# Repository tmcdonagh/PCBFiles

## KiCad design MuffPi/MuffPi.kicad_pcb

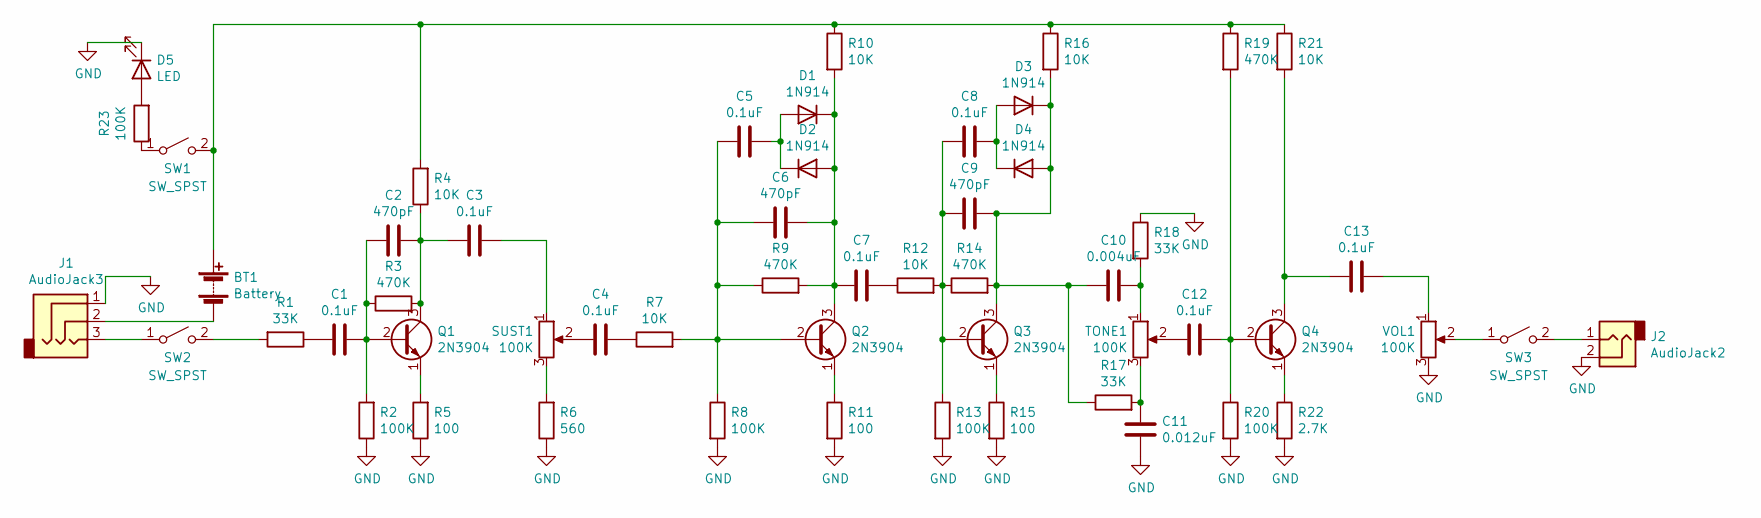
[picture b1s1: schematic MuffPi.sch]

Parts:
BT1: Battery; PinHeader_1x02_P2.00mm_Vertical
C1, C3, C4, C5, C7, C8, C12, C13: 0.1uF; C_Disc_D4.7mm_W2.5mm_P5.00mm
C2, C6, C9: 470pF; C_Disc_D4.3mm_W1.9mm_P5.00mm
C10: 0.004uF; C_Disc_D4.3mm_W1.9mm_P5.00mm
C11: 0.012uF; C_Disc_D4.3mm_W1.9mm_P5.00mm
D1, D2, D3, D4: 1N914; D_DO-35_SOD27_P7.62mm_Horizontal
D5: LED; LED_D3.0mm
J1: AudioJack3; PinHeader_1x03_P2.00mm_Vertical
J2: AudioJack2; PinHeader_1x02_P2.00mm_Vertical
Q1, Q2, Q3, Q4: 2N3904; TO-92_Inline
R1, R17, R18: 33K; R_Axial_DIN0207_L6.3mm_D2.5mm_P10.16mm_Horizontal
R2, R8, R13, R20, R23: 100K; R_Axial_DIN0207_L6.3mm_D2.5mm_P10.16mm_Horizontal
R3, R9, R14, R19: 470K; R_Axial_DIN0207_L6.3mm_D2.5mm_P10.16mm_Horizontal
R4, R7, R10, R12, R16, R21: 10K; R_Axial_DIN0207_L6.3mm_D2.5mm_P10.16mm_Horizontal
R5, R11, R15: 100; R_Axial_DIN0207_L6.3mm_D2.5mm_P10.16mm_Horizontal
R6: 560; R_Axial_DIN0207_L6.3mm_D2.5mm_P10.16mm_Horizontal
R22: 2.7K; R_Axial_DIN0207_L6.3mm_D2.5mm_P10.16mm_Horizontal
SUST1: 100K; PinHeader_1x03_P2.00mm_Vertical
SW1, SW2, SW3: SW_SPST; PinHeader_1x02_P2.00mm_Vertical
TONE1: 100K; PinHeader_1x03_P2.00mm_Vertical
VOL1: 100K; PinHeader_1x03_P2.00mm_Vertical

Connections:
GND: C11.1, D5.1 (K), J1.1, J2.2, R2.1, R5.1, R6.1, R8.2, R11.2, R13.2, R15.2, R18.1, R20.2, R22.2, VOL1.3
unnamed: BT1.1 (+), R4.2, R10.1, R16.1, R19.1, R21.1, SW1.2 (B)
unnamed: BT1.2 (-), J1.2
unnamed: C1.1, C2.2, Q1.2 (B), R2.2, R3.1
unnamed: C1.2, R1.1
unnamed: C2.1, C3.2, Q1.3 (C), R3.2, R4.1
unnamed: C3.1, SUST1.1
unnamed: C4.1, R7.1
unnamed: C4.2, SUST1.2
unnamed: C5.1, D1.2 (A), D2.1 (K)
unnamed: C5.2, C6.2, Q2.2 (B), R7.2, R8.1, R9.1
unnamed: C6.1, C7.2, D1.1 (K), D2.2 (A), Q2.3 (C), R9.2, R10.2
unnamed: C7.1, R12.1
unnamed: C8.1, D3.2 (A), D4.1 (K)
unnamed: C8.2, C9.2, Q3.2 (B), R12.2, R13.1, R14.1
unnamed: C10.1, R18.2, TONE1.1
unnamed: C9.1, C10.2, D3.1 (K), D4.2 (A), Q3.3 (C), R14.2, R16.2, R17.1
unnamed: C11.2, R17.2, TONE1.3
unnamed: C12.1, TONE1.2
unnamed: C12.2, Q4.2 (B), R19.2, R20.1
unnamed: C13.1, Q4.3 (C), R21.2
unnamed: C13.2, VOL1.1
unnamed: D5.2 (A), R23.2
unnamed: J1.3, SW2.1 (A)
unnamed: J2.1, SW3.2 (B)
unnamed: Q1.1 (E), R5.2
unnamed: Q2.1 (E), R11.1
unnamed: Q3.1 (E), R15.1
unnamed: Q4.1 (E), R22.1
unnamed: R1.2, SW2.2 (B)
unnamed: R6.2, SUST1.3
unnamed: R23.1, SW1.1 (A)
unnamed: SW3.1 (A), VOL1.2

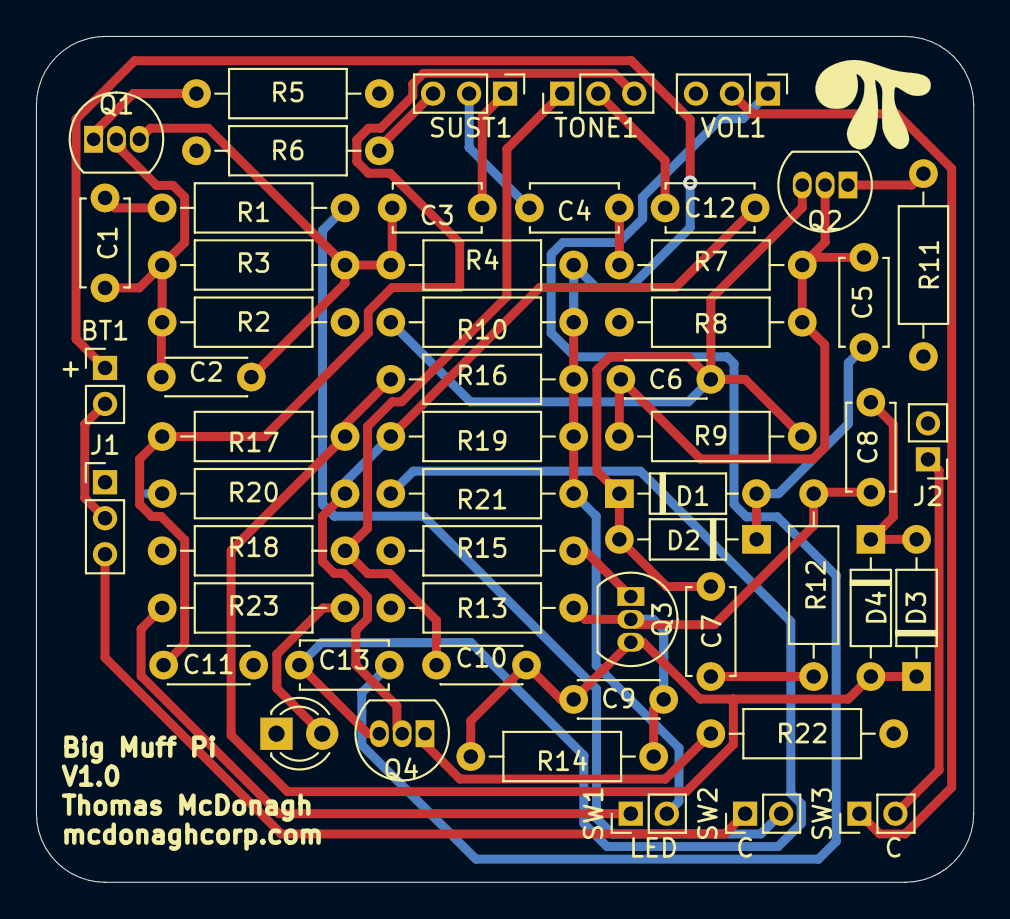
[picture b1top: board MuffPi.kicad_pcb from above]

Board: 2 copper layers, 52.1 x 47.0 mm, 54 parts (0 on the bottom side), 33 nets.

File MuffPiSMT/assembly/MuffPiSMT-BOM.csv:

Value,Designator,Footprint,LCSC Part #
100nF,"C1,C3,C4,C5,C7,C8,C12,C13",0603,C14663
4.7nF,C10,0603,C53987
0.012uF,C11,0603,C1593
470pF,"C2,C6,C9",0603,C1620
1N914,"D1,D2,D3,D4",SOD-323F,C258181
2N3904,"Q1,Q2,Q3,Q4",SOT-23-3,C18536
33K,"R1,R17,R18",0603,C4216
100K,"R2,R8,R13,R20,R23",0603,C25803
2.7K,R22,0603,C13167
470K,"R3,R9,R14,R19",0603,C23178
10K,"R4,R7,R10,R12,R16,R21",0603,C25804
100,"R5,R11,R15",0603,C7250
560,R6,0603,C23189
,,,
,,,
,,,
,,,

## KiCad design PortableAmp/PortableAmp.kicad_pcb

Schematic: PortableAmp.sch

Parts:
C1: 100uF; CP_Axial_L18.0mm_D6.5mm_P25.00mm_Horizontal
C2, C4: 47nF; C_Flat_L7.2_H6.5
C3: 100nF; C_Flat_L7.2_H6.5
C5: 220uF; CP_Axial_L10.0mm_D6.0mm_P15.00mm_Horizontal
D1: D; D_DO-41_SOD81_P10.16mm_Horizontal
H1, H2, H3, H4: Mount; MountingHole_2.7mm_Pad
J1: Conn_01x04_Male; PinSocket_1x04_P2.54mm_Vertical
J2: Speaker; PinSocket_1x02_P2.54mm_Vertical
Q1: MPF102; TO-92L_Inline
R1: 1.5M; R_Axial_DIN0207_L6.3mm_D2.5mm_P10.16mm_Horizontal
R2: 3.9K; R_Axial_DIN0207_L6.3mm_D2.5mm_P10.16mm_Horizontal
R3: 10; R_Axial_DIN0207_L6.3mm_D2.5mm_P10.16mm_Horizontal
RV1: 10K-B; Potentiometer_Bourns_3386F_Vertical
RV2: 1K-B; Potentiometer_Bourns_3386F_Vertical
SW1: Power; PinHeader_1x02_P2.54mm_Vertical
U1: LM386; DIP-8_W7.62mm

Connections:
9V: J1.4, SW1.1
GND: C1.2, C3.1, C4.2, H1.1, H2.1, H3.1, H4.1, J1.1, J1.2, J2.1, R1.2, R2.2, RV1.1, U1.3 (+), U1.4 (GND)
Input: J1.3, Q1.3 (G), R1.1
unnamed: C1.1, D1.1 (K), Q1.1 (D), U1.6 (V+)
unnamed: C2.1, Q1.2 (S), R2.1
unnamed: C2.2, RV1.3
unnamed: C3.2, U1.7 (BYPASS)
unnamed: C4.1, R3.2
unnamed: C5.1, R3.1, U1.5
unnamed: C5.2, J2.2
unnamed: D1.2 (A), SW1.2
unnamed: RV1.2, U1.2 (-)
unnamed: RV2.1, U1.8 (GAIN)
unnamed: RV2.2, RV2.3, U1.1 (GAIN)

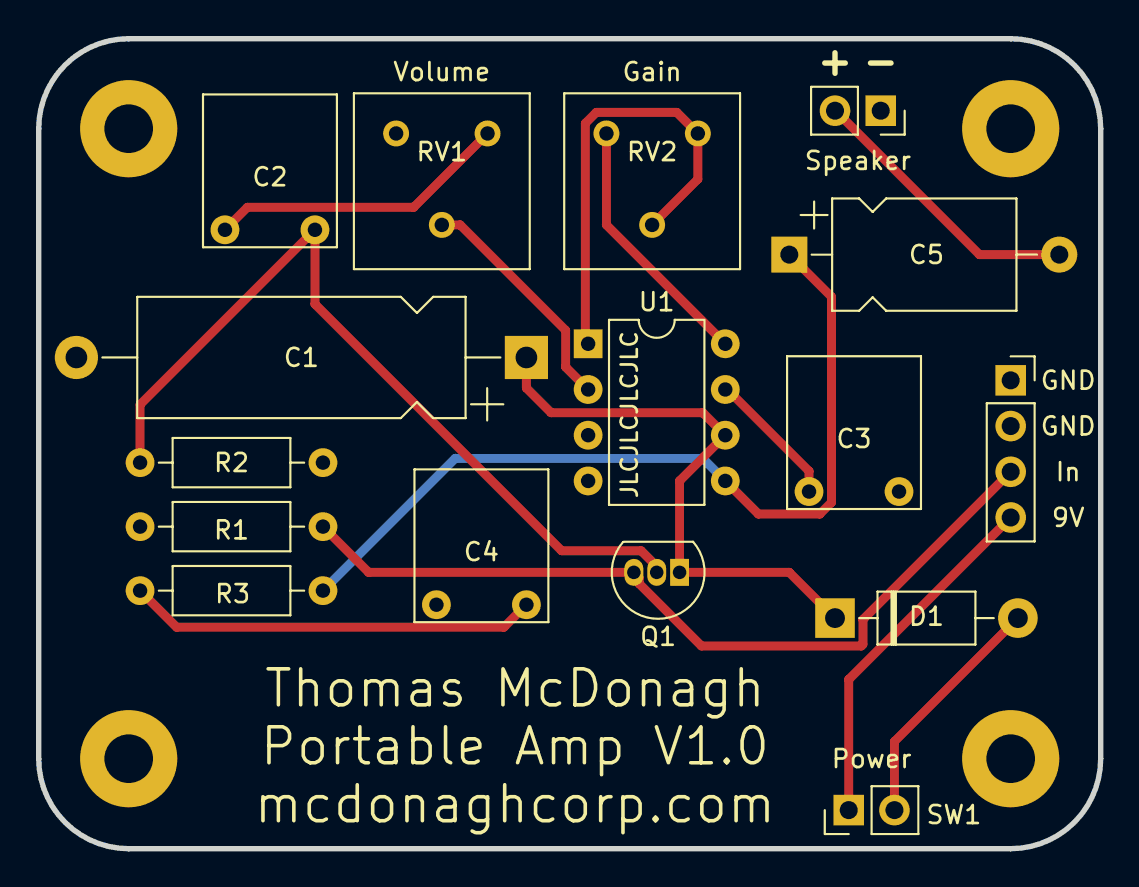
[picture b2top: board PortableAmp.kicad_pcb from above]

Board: 2 copper layers, 59.0 x 45.0 mm, 20 parts (0 on the bottom side), 14 nets.

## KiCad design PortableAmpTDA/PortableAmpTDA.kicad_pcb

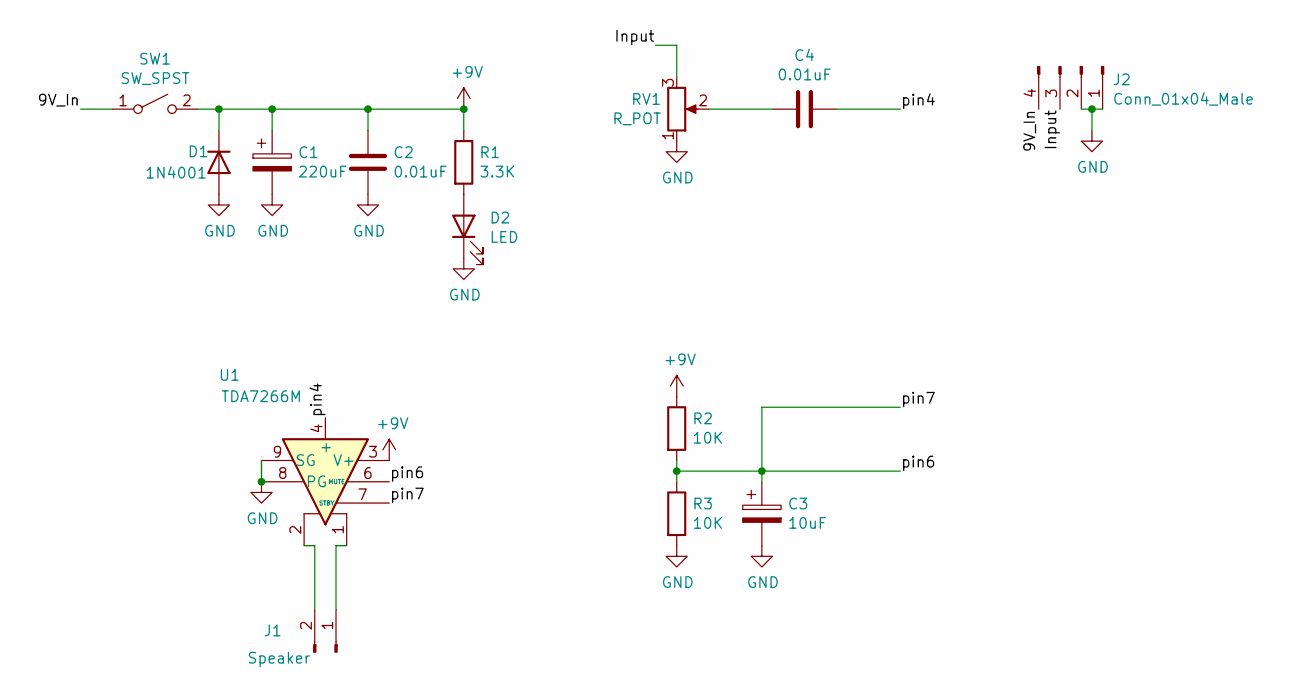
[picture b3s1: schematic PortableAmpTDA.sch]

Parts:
C1: 220uF; CP_Radial_D6.3mm_P2.50mm
C2, C4: 0.01uF; C_Flat_L7.2_H6.5
C3: 10uF; CP_Axial_L10.0mm_D6.0mm_P15.00mm_Horizontal
D1: 1N4001; D_DO-41_SOD81_P10.16mm_Horizontal
D2: LED; LED_D5.0mm
J1: Speaker; PinSocket_1x02_P2.54mm_Vertical
J2: Conn_01x04_Male; PinSocket_1x04_P2.54mm_Vertical
R1: 3.3K; R_Axial_DIN0207_L6.3mm_D2.5mm_P10.16mm_Horizontal
R2, R3: 10K; R_Axial_DIN0207_L6.3mm_D2.5mm_P10.16mm_Horizontal
RV1: R_POT; PinSocket_1x03_P2.54mm_Vertical
SW1: SW_SPST; PinSocket_1x02_P2.54mm_Vertical
U1: TDA7266M; TO-220-15_P2.54x2.54mm_StaggerOdd_Lead4.58mm_Vertical

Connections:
+9V: C1.1, C2.1, D1.1 (K), R1.1, R2.1, SW1.2 (B), U1.3 (V+), U1.13 (V+)
/9V_In: J2.4, SW1.1 (A)
/Input: J2.3, RV1.3
/pin4: C4.1, U1.4 (+)
/pin6: C3.1, R2.2, R3.1, U1.6 (MUTE), U1.7 (STBY)
GND: C1.2, C2.2, C3.2, D1.2 (A), D2.1 (K), J2.1, J2.2, R3.2, RV1.1, U1.8 (PG), U1.9 (SG)
unnamed: C4.2, RV1.2
unnamed: D2.2 (A), R1.2
unnamed: J1.1, U1.1
unnamed: J1.2, U1.2

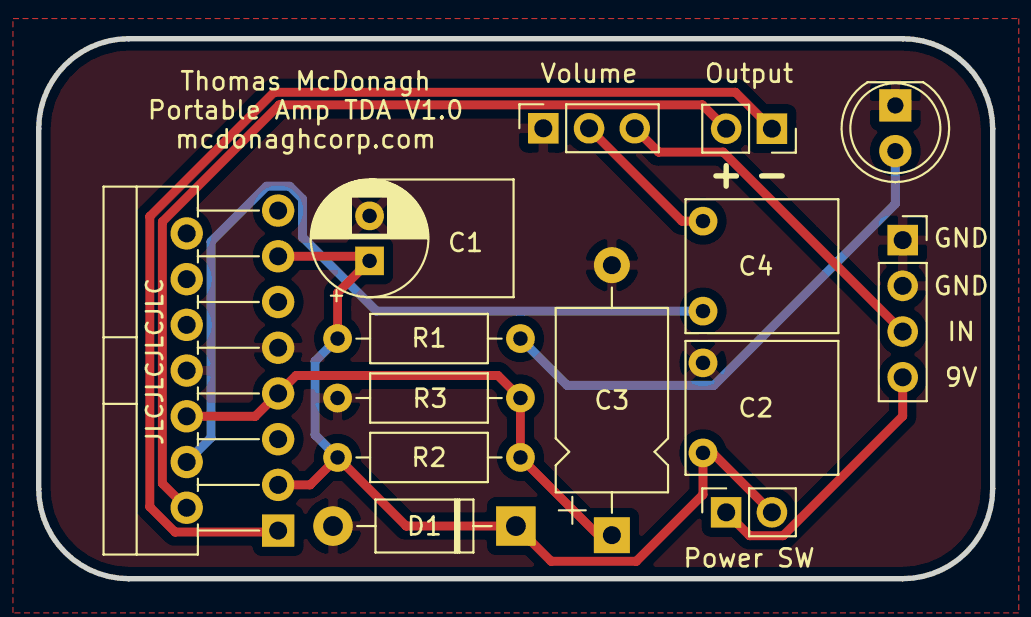
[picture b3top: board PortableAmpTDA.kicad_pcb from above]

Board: 2 copper layers, 53.0 x 30.0 mm, 14 parts (0 on the bottom side), 10 nets.

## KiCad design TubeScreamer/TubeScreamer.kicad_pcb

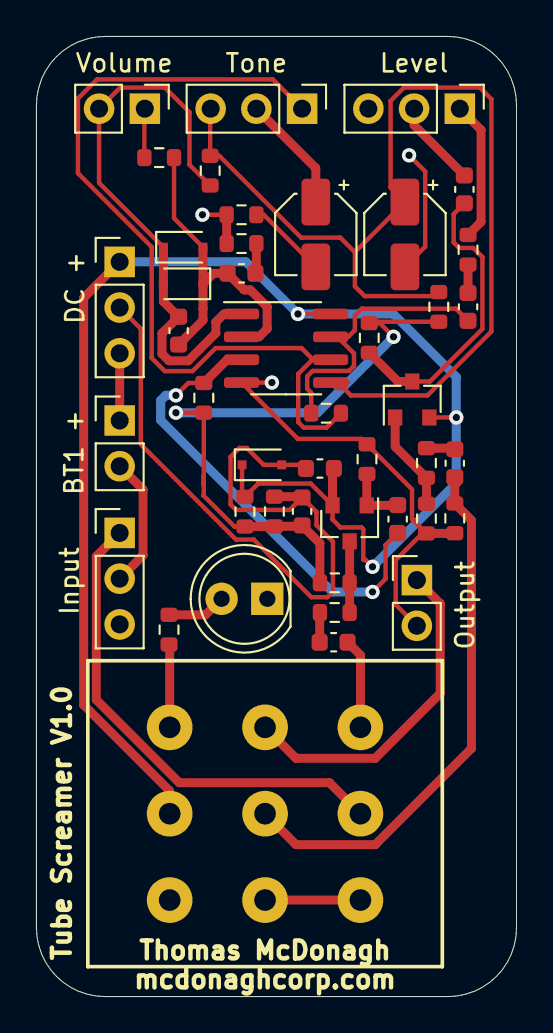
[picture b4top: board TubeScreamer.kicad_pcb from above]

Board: 2 copper layers, 26.7 x 53.3 mm, 44 parts (0 on the bottom side), 32 nets.

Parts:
BT1 +: 9V; PinHeader_1x02_P2.54mm_Vertical
C1: 0.02uF; C_0603_1608Metric
C2: 100F/10V; C_0603_1608Metric
C3: 47F/10V; C_0603_1608Metric
C4, C9: 1uF/50V; C_0603_1608Metric
C5: 0.047uF; C_0603_1608Metric
C6: 51pF; C_0603_1608Metric
C7: 0.22/35V; CP_Elec_4x5.3
C8: 0.22; CP_Elec_4x5.3
C10: 0.1; C_0603_1608Metric
C11: 10uF/16V; C_0603_1608Metric
D1, D2, D3: 1N914; D_SOD-323F
D4: LED; LED_D5.0mm
DC +: Barrel_Jack_Switch; PinHeader_1x03_P2.54mm_Vertical
Input: AudioJack3; PinHeader_1x03_P2.54mm_Vertical
Level: Level 100K; PinHeader_1x03_P2.54mm_Vertical
Output: AudioJack2; PinHeader_1x02_P2.54mm_Vertical
Q1, Q2: 2SC1815; SOT-23
R1, R9, R12, R13: 1K; R_0603_1608Metric
R2, R14: 510K; R_0603_1608Metric
R3, R4, R5, R7, R11, R15, R17: 10K; R_0603_1608Metric
R6: 4.7K; R_0603_1608Metric
R8: 51K; R_0603_1608Metric
R10: 220; R_0603_1608Metric
R16: 100; R_0603_1608Metric
R18: 100K; R_0603_1608Metric
S1: SWITCH-3PDT-PTH-STOMP; STOMP_SWITCH_3PDT
Tone: Tone 20K; PinHeader_1x03_P2.54mm_Vertical
U1: Opamp_Dual_Generic; SOIC-8_3.9x4.9mm_P1.27mm
Volume: Distortion 500K Log; PinHeader_1x02_P2.54mm_Vertical

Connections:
4V5: C3.2, R2.2, R4.1, R5.2, R7.2, R11.2, R14.2
+9V: C2.2, D1.1, DC +.1, Q1.2, Q2.2, R4.2, S1.P$8, U1.8
GND: C7.2, D4.1, Input.3, Level.3, Output.2, R3.1, R6.2, R10.2, R15.1, R17.2, U1.4
unnamed: BT1 +.1, DC +.3
unnamed: BT1 +.2, Input.2
unnamed: C1.1, S1.P$3
unnamed: C1.2, R1.2
unnamed: C2.1, C3.1, D1.2, DC +.2, R5.1
unnamed: C4.1, Q1.1, R3.2
unnamed: C4.2, R7.1, U1.3
unnamed: C5.1, R6.1
unnamed: C5.2, C6.1, D2.2, D3.1, R8.1, U1.2
unnamed: C6.2, D2.1, D3.2, R9.2, U1.1, Volume.2
unnamed: C7.1, R9.1, R11.1, Tone.3, U1.5
unnamed: C8.1, Tone.2
unnamed: C8.2, R10.1
unnamed: C9.1, R13.2
unnamed: C9.2, R12.2, U1.7
unnamed: C10.1, Q2.3, R14.1
unnamed: C10.2, Level.2
unnamed: C11.1, R17.1, S1.P$5
unnamed: C11.2, R16.2
unnamed: D4.2, R18.2
unnamed: Input.1, S1.P$2
unnamed: Output.1, S1.P$6
unnamed: R8.2, Volume.1
unnamed: R12.1, Tone.1, U1.6
unnamed: Level.1, R13.1
unnamed: Q1.3, R1.1, R2.1
unnamed: Q2.1, R15.2, R16.1
unnamed: R18.1, S1.P$9
unnamed: S1.P$1, S1.P$4

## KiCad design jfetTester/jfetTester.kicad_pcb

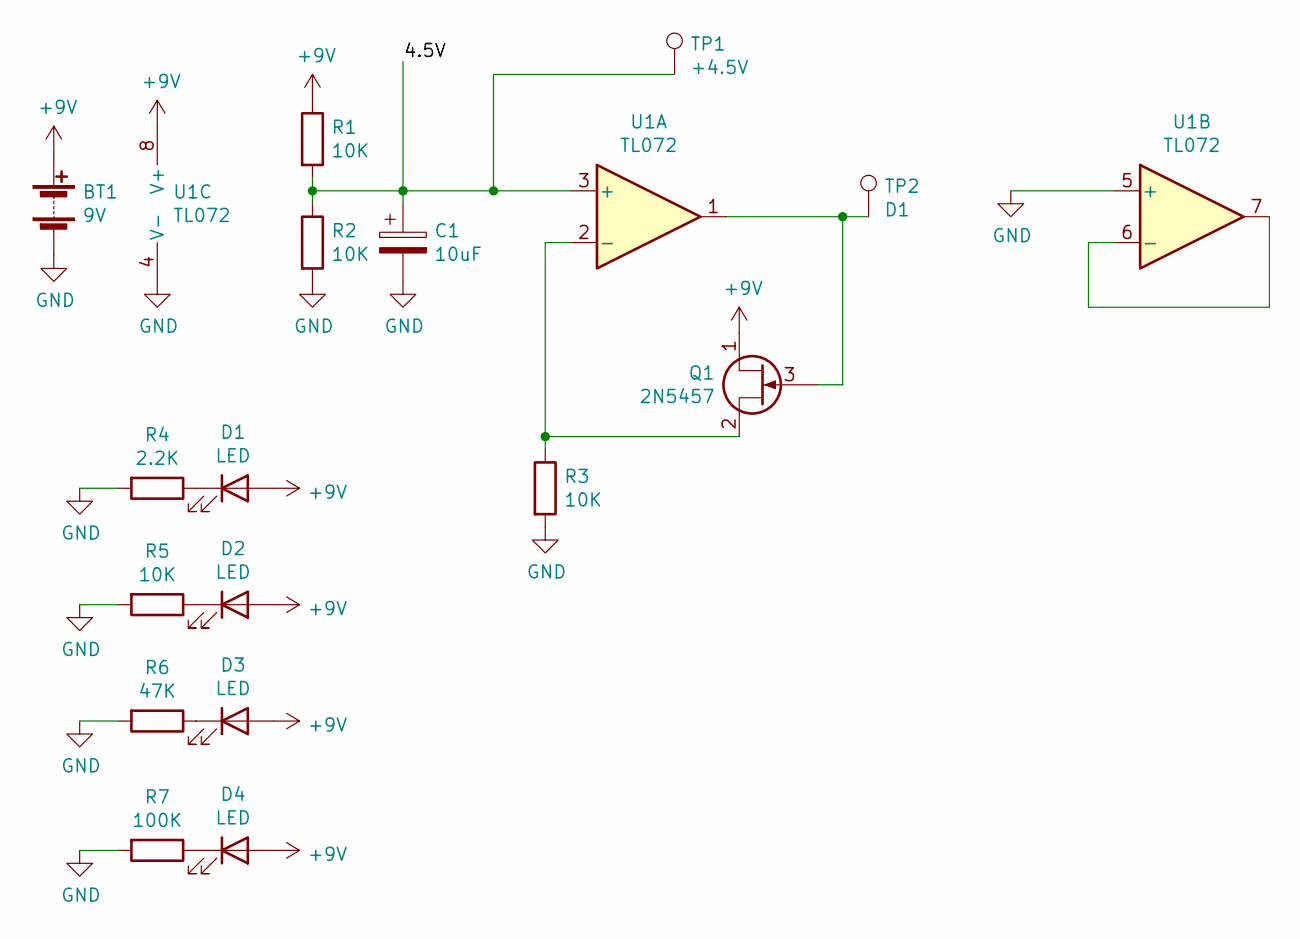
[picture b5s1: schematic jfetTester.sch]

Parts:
BT1: 9V; PinSocket_1x02_P2.54mm_Vertical
C1: 10uF; CP_Radial_D6.3mm_P2.50mm_L11.0mm
D1, D2, D3, D4: LED; LED_D5.0mm
Q1: 2N5457; TO-92_Inline
R1, R2, R3, R5: 10K; R_Axial_DIN0207_L6.3mm_D2.5mm_P10.16mm_Horizontal
R4: 2.2K; R_Axial_DIN0207_L6.3mm_D2.5mm_P10.16mm_Horizontal
R6: 47K; R_Axial_DIN0207_L6.3mm_D2.5mm_P10.16mm_Horizontal
R7: 100K; R_Axial_DIN0207_L6.3mm_D2.5mm_P10.16mm_Horizontal
TP1: +4.5V; TestPoint_Loop_D3.50mm_Drill1.4mm_Beaded
TP2: D1; TestPoint_Loop_D3.50mm_Drill1.4mm_Beaded
U1: TL072; DIP-8_W7.62mm_Socket

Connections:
+9V: BT1.1 (+), D1.2 (A), D2.2 (A), D3.2 (A), D4.2 (A), Q1.1 (D), R1.1, U1.8 (V+)
/4.5V: C1.1, R1.2, R2.1, TP1.1, U1.3 (+)
GND: BT1.2 (-), C1.2, R2.2, R3.2, R4.2, R5.2, R6.2, R7.2, U1.4 (V-), U1.5 (+)
unnamed: D1.1 (K), R4.1
unnamed: D2.1 (K), R5.1
unnamed: D3.1 (K), R6.1
unnamed: D4.1 (K), R7.1
unnamed: Q1.2 (S), R3.1, U1.2 (-)
unnamed: Q1.3 (G), TP2.1, U1.1
unnamed: U1.6 (-), U1.7

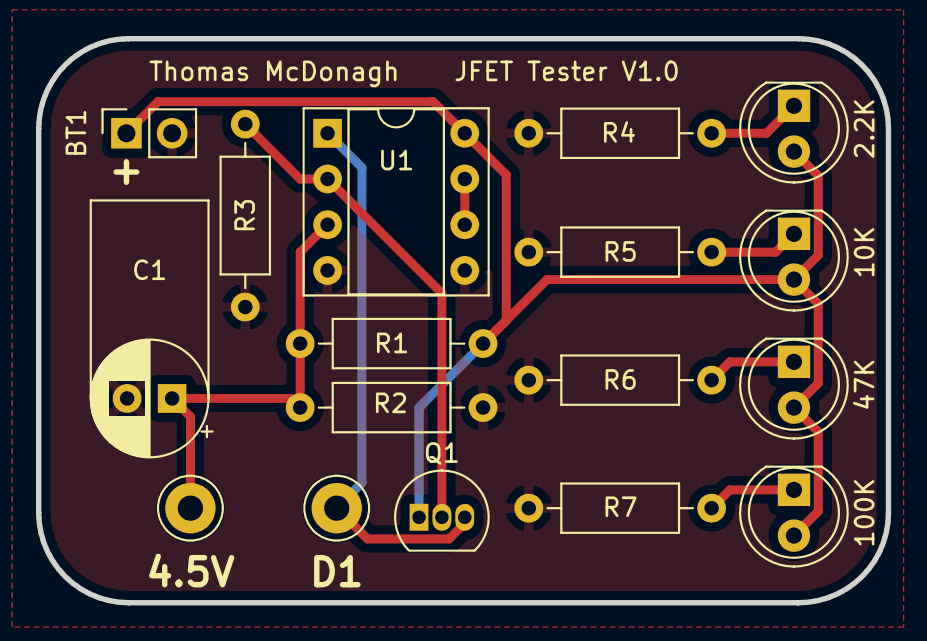
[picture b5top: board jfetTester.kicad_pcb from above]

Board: 2 copper layers, 47.2 x 31.3 mm, 17 parts (0 on the bottom side), 10 nets.
